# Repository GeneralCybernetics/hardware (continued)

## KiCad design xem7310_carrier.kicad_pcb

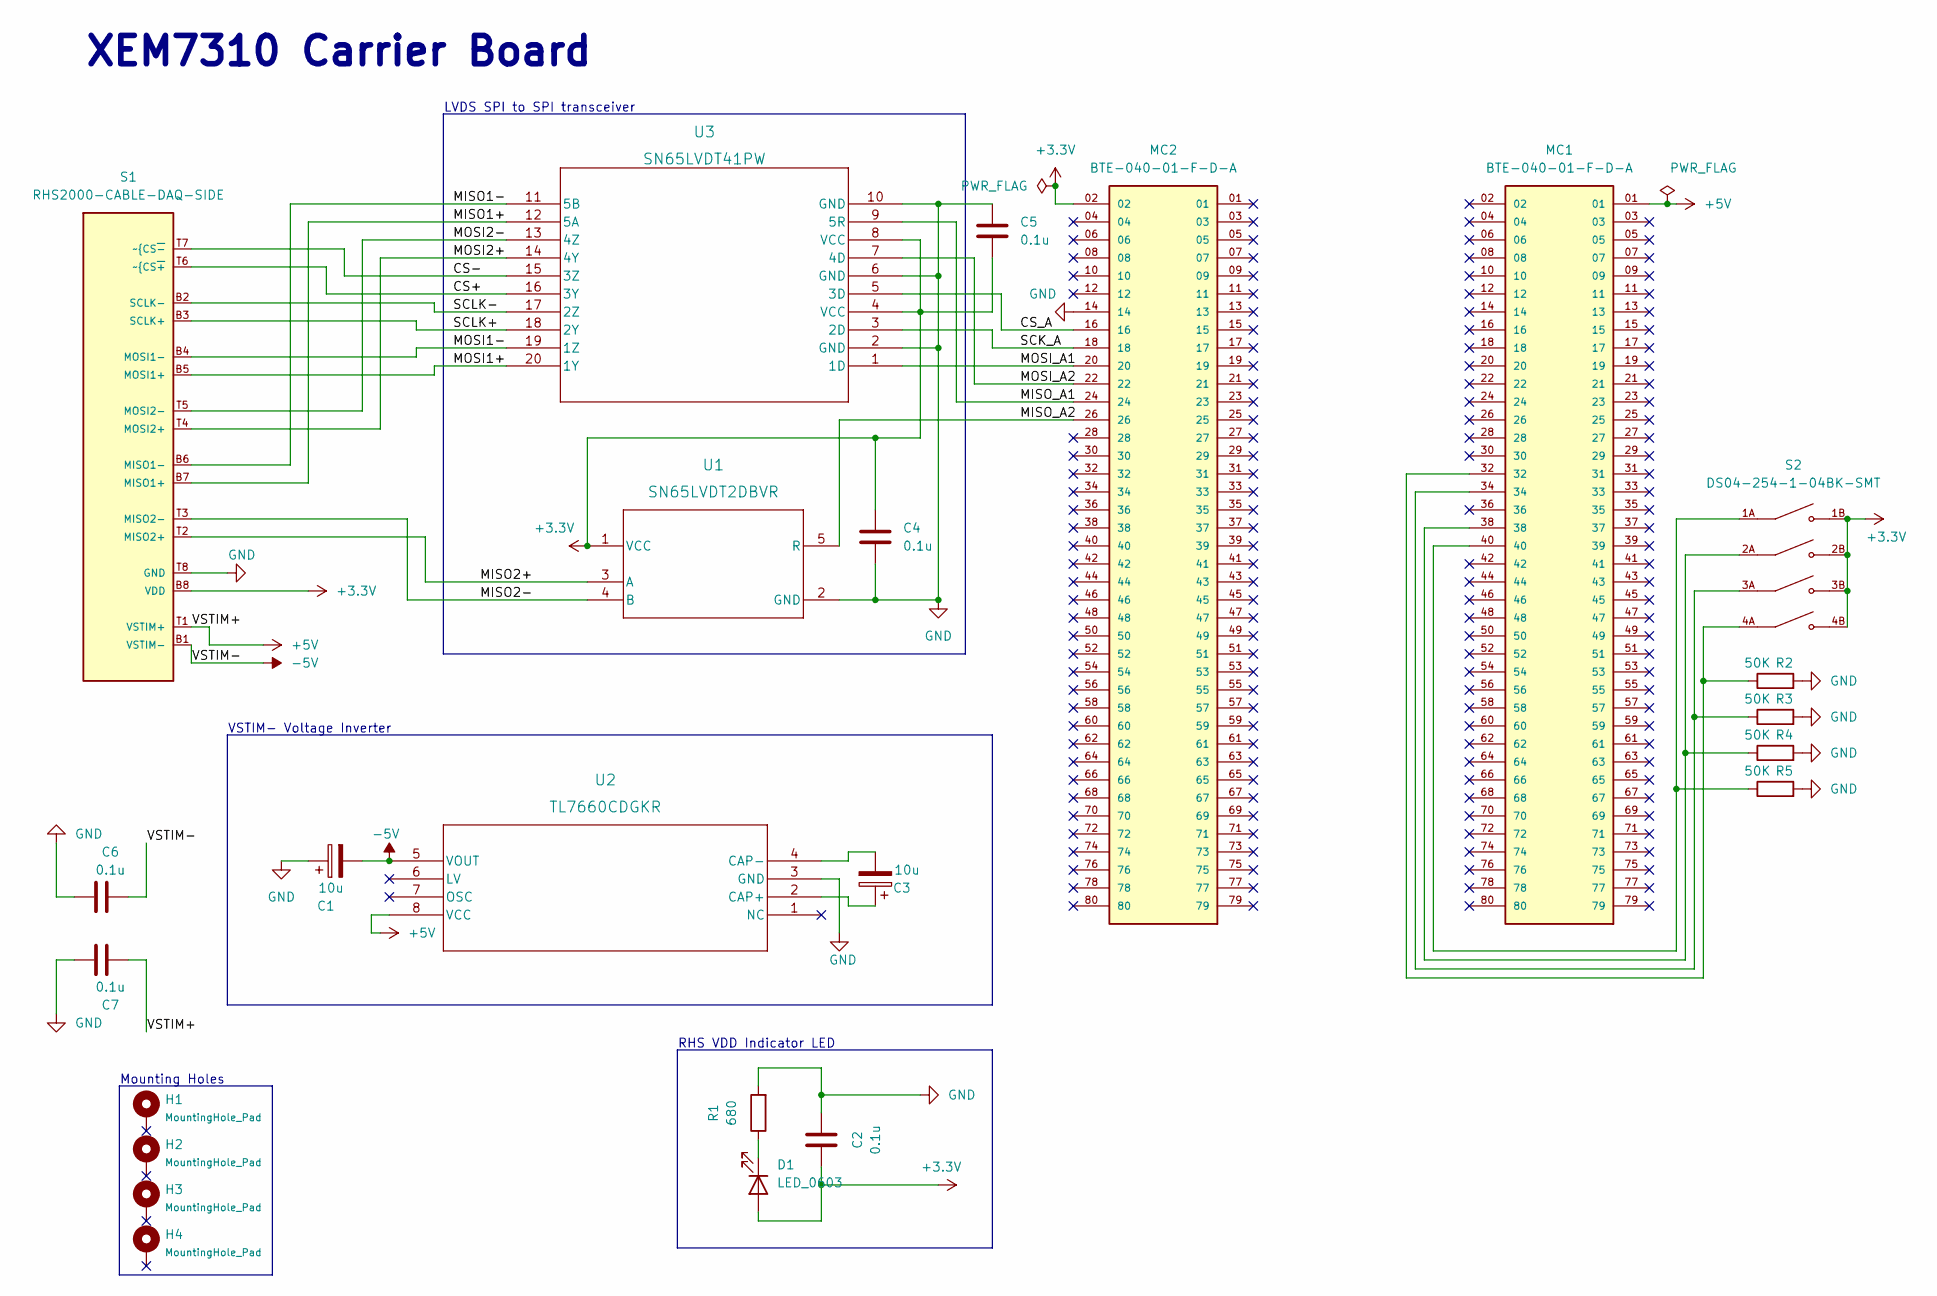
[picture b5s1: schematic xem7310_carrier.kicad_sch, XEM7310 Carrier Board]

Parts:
C1, C3: 10u; CP_Elec_4x5.4
C2, C4, C5, C6, C7: 0.1u; C_0402_1005Metric
D1: LED_0603; LED_0603_1608Metric
H1, H2, H3, H4: MountingHole_Pad; MountingHole_2.7mm_M2.5_DIN965_Pad
MC1, MC2: BTE-040-01-F-D-A; SAMTEC_BTE-040-01-F-D-A; PARTREV R
R1: 680; R_0603_1608Metric
R2, R3, R4, R5: 50K; R_0603_1608Metric
S1: RHS2000-CABLE-DAQ-SIDE
S2: DS04-254-1-04BK-SMT; SW_DS04-254-1-04BK-SMT; PARTREV V0.0
U1: SN65LVDT2DBVR; DBV0005A_N
U2: TL7660CDGKR; DGK8
U3: SN65LVDT41PW; PW20

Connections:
+3.3V: C2.2, C4.1, C5.2, D1.2 (A), MC2.02, S1.B8 (VDD), S2.1B, S2.2B, S2.3B, S2.4B, U1.1 (VCC), U3.4 (VCC), U3.8 (VCC)
+5V: C7.2, MC1.01, S1.T1 (VSTIM+), U2.8 (VCC)
-5V: C1.2, C6.2, S1.B1 (VSTIM-), U2.5 (VOUT)
/CS+: S1.T6 (~CS~{+), U3.16 (3Y)
/CS-: S1.T7 (~CS~{-), U3.15 (3Z)
/CS_A: MC2.16, U3.5 (3D)
/MISO1+: S1.B7 (MISO1+), U3.12 (5A)
/MISO1-: S1.B6 (MISO1-), U3.11 (5B)
/MISO2+: S1.T2 (MISO2+), U1.3 (A)
/MISO2-: S1.T3 (MISO2-), U1.4 (B)
/MISO_A1: MC2.24, U3.9 (5R)
/MISO_A2: MC2.26, U1.5 (R)
/MOSI1+: S1.B5 (MOSI1+), U3.20 (1Y)
/MOSI1-: S1.B4 (MOSI1-), U3.19 (1Z)
/MOSI2+: S1.T4 (MOSI2+), U3.14 (4Y)
/MOSI2-: S1.T5 (MOSI2-), U3.13 (4Z)
/MOSI_A1: MC2.20, U3.1 (1D)
/MOSI_A2: MC2.22, U3.7 (4D)
/SCK_A: MC2.18, U3.3 (2D)
/SCLK+: S1.B3 (SCLK+), U3.18 (2Y)
/SCLK-: S1.B2 (SCLK-), U3.17 (2Z)
GND: C1.1, C2.1, C4.2, C5.1, C6.1, C7.1, MC2.14, R1.2, R2.2, R3.2, R4.2, R5.2, S1.T8 (GND), U1.2 (GND), U2.3 (GND), U3.2 (GND), U3.6 (GND), U3.10 (GND)
unnamed: C3.1, U2.2 (CAP+)
unnamed: C3.2, U2.4 (CAP-)
unnamed: MC1.32, R2.1, S2.4A
unnamed: MC1.34, R3.1, S2.3A
unnamed: MC1.38, R4.1, S2.2A
unnamed: MC1.40, R5.1, S2.1A
unnamed: D1.1 (K), R1.1

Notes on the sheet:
XEM7310 Carrier Board
Mounting Holes
RHS VDD Indicator LED
LVDS SPI to SPI transceiver
VSTIM- Voltage Inverter

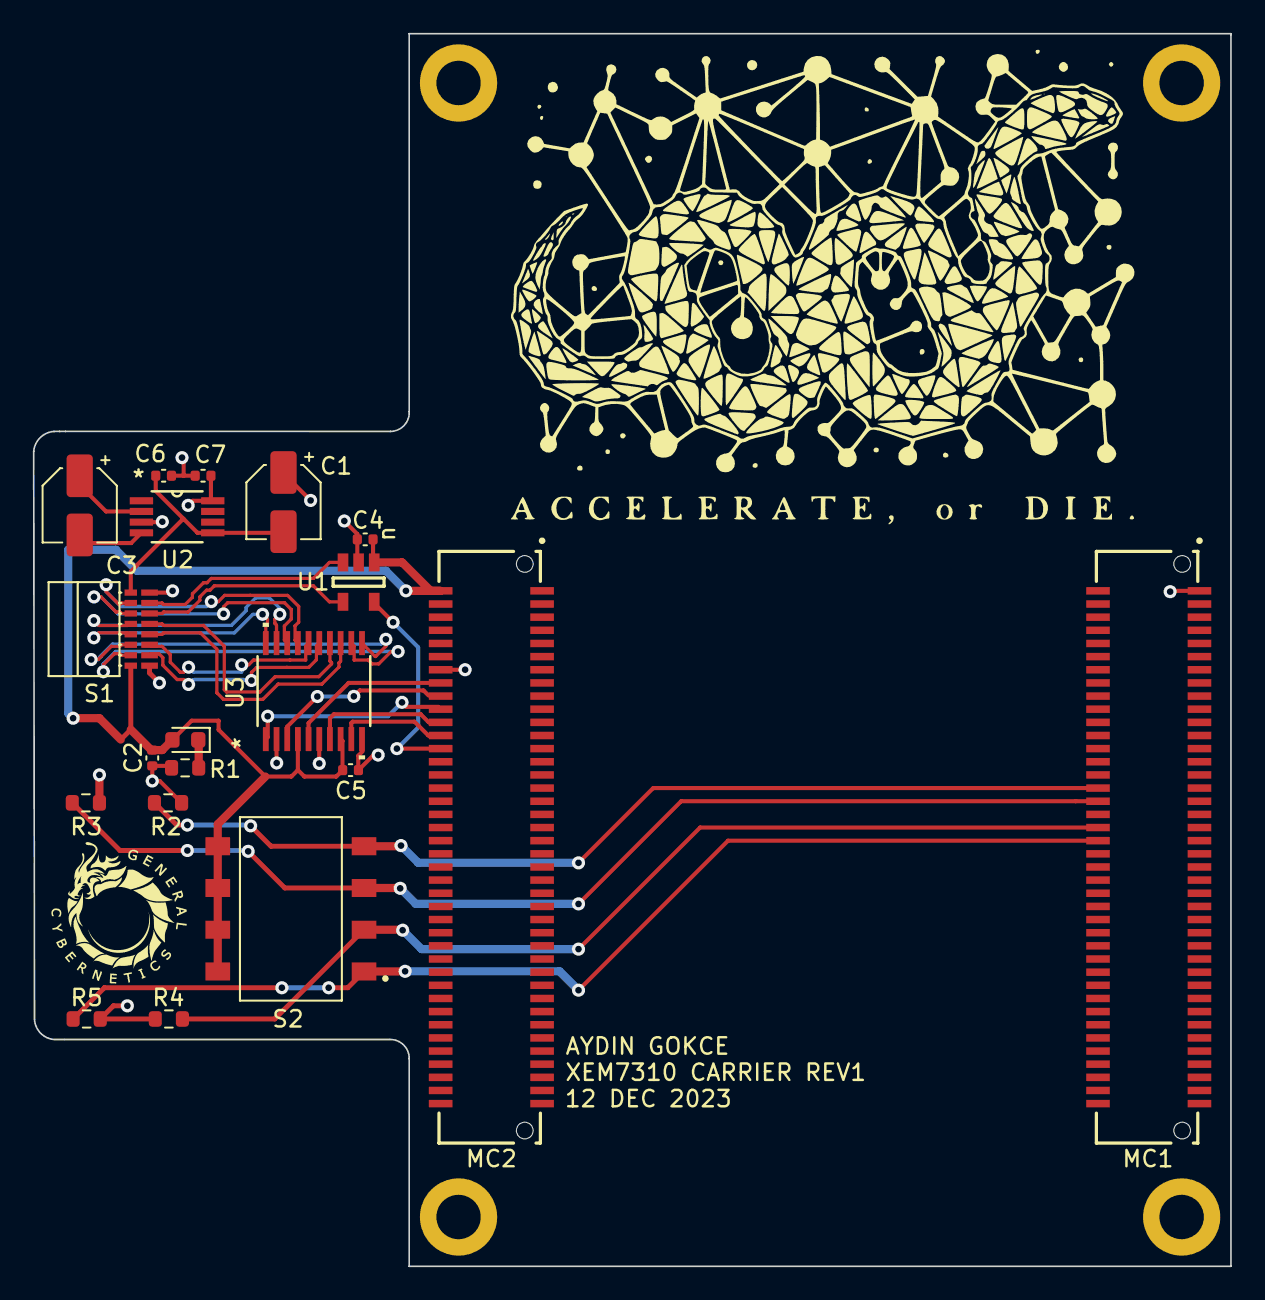
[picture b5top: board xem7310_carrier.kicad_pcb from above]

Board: 4 copper layers, 72.8 x 75.0 mm, 24 parts (0 on the bottom side), 29 nets.

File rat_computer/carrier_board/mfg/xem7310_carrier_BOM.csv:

Comment,Designator,Footprint,"Cost (total, est.)",Notes,Purchase & Datasheet Link
10u,"C1, C3",Capacitor_SMD:CP_Elec_4x5.4,~,Polarized Capacitor,~
0.1u,"C2, C4, C5, C6, C7",Capacitor_SMD:C_0402_1005Metric,~,~,~
LED_0603,D1,LED_SMD:LED_0603_1608Metric,~,Color Green,~
BTE-040-01-F-D-A,"MC1, MC2",BTE-040-01-F-D-A:SAMTEC_BTE-040-01-F-D-A,$17.20,~,https://www.digikey.com/en/products/detail/samtec-inc/BTE-04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
680,R1,Resistor_SMD:R_0603_1608Metric,~,~,~
50K,"R2, R3, R4, R5",Resistor_SMD:R_0603_1608Metric,~,~,~
RHS2000-CABLE-DAQ-SIDE,S1,OMNETICS_PZN-16-AA,$47.48,EXCLUDE FROM ASSEMBLY,~
DS04-254-1-04BK-SMT,S2,DS04-254-1-04BK-SMT:SW_DS04-254-1-04BK-SMT,$0.87,~,https://www.mouser.com/ProductDetail/CUI-Devices/DS04-254-1-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
SN65LVDT2DBVR,U1,FP_LVDT2:DBV0005A_N,$1.85,SOT-23 package,https://www.digikey.com/en/products/detail/texas-instruments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
TL7660CDGKR,U2,TP_TL7660:DGK8,$1.54,8-VSSOP package,https://www.digikey.com/en/products/detail/texas-instruments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
SN65LVDT41PW,U3,FP_LVDT41:PW20,$7.60,20-TSSOP package,https://www.digikey.com/en/products/detail/texas-instruments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

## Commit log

2024-01-04 carrier board
2024-01-17 mea breakout board
2024-01-24 fix: removed soldermask covering pads, lay rows out in the correct square shape
2024-01-26 changed soldermask to black, exported step files
2024-01-26 *actually added step files
2024-01-28 designed carrier board for mp-highdriver
2024-03-14 added keep aliveanator PCB altium project package
2024-08-02 alignment stage done
2024-08-02 completed PT assay led seqs
2024-08-10 EK – microfluidics chip design + documentation
2024-08-10 Changed name of design
2024-08-11 v1.5 updated with full documentation
2024-08-11 Added the md rfc in rfc_md
2024-08-11 removed v1
2024-08-13 refactor: added project-specific subdirectories, added ion concentration biomodulato
2024-08-13 pushing v6
2024-08-13 pushing v7
2024-08-13 refactor: cleanup silkscreen designators
2024-08-13 fix: left-sided highdriver4 pinout (schematic)
2024-08-13 pushing minor v7 changes
2024-08-13 Fix: Switched LED for an 0603 diode
2024-08-16 finished v7 (cleared by DRC)
2024-08-16 V7 fix: Increased area to add mounting holes and pushed receptacles to the edge of board
2024-08-17 Fix: Pulled out the
2024-08-17 Fix: Swapped ground and power planes
2024-08-17 gitignore
2024-08-18 added JLCPCB constraints and gitignore updates
2024-08-18 fix(icbm): update tolerances to comply with new dru
2024-08-18 refactor(icbm): improve capacitor placement
2024-08-18 fix: started adding footprint, symbol and 3dmodel libraries
2024-08-18 Added scripts to improve quality of life when working between remote repo and local KiCAD
2024-08-18 Pushed project_library parser
2024-08-18 Testing add_project_libraries.sh
2024-08-18 Migrated to remote repository use, changing footprints to relative paths
2024-08-18 added co2 sensor 3d model
2024-08-18 pushed all components step files (except 1) for icbm
2024-08-18 fix: moved peltier and co2 solenoid further apart from each other to fit them
2024-08-18 improvements to add_project_libraries.sh
2024-08-18 Finished add_project_libraries script
2024-08-19 fix: Script now asks for input for local file path
2024-08-19 init
2024-08-19 Pushed net changes to v7 ICBM
2024-08-19 testing libraries
2024-08-20 refactor: remove macos malware
2024-08-20 refactor: rearranged everything so it makes sense
2024-08-20 refactor: removed dropped project (for now)
2024-08-20 chore: remove macos malware
2024-08-20 README.md
2024-08-20 feat: automatic project generation
2024-08-20 fix: unfucked footprint and symbol tables
2024-08-22 creating legacy branch before project restructure
2024-08-22 saving before merge
2024-08-22 fix: replaced the USB connector with one in the JLCPCB parts library
2024-08-22 fix: removed macos malware
2024-08-22 feat: delete footprint cache when updating libraries
2024-08-22 fix: Delete .DS_Store
2024-08-22 fix: symlinked common files
2024-08-22 fix: absolute path symlinks -> relative path symlinks
2024-08-22 ci: added anush's components
2024-08-22 fix: refresh libraries script breaking when not in common/kicad
2024-08-24 fix: symbol and footprint libs, and improved routing
2024-08-24 refactor: re-routed icbm
2024-08-24 mfg file for 0.0.8
2024-08-28 fix: move N-channel FETs from high-side to low-side configuration
2024-08-28 fix: ERC errors
2024-08-28 chore: routed MOSFET fixes
2024-08-30 update mfg files
2024-09-01 bioreactor microfluidic chip and keep-aliveinator
2024-09-01 solidworks init
2024-09-01 fix: replace fridge peltier cooler FET with an h-bridge
2024-09-01 chore: specify STEP file
2024-09-01 finished schematic for DC/DC inverter
2024-09-01 updated table with opamp
2024-09-05 designed box & fridge holder
2024-09-05 shrunk lid size, some fixes
2024-09-05 solidworks session wrap-up
2024-09-06 chore: readme update
2024-09-08 ci: main AC/DC schematic done minus incubator peripherals
2024-09-15 fix: added new STM32 with 3 DAC output pins
2024-09-15 ci: added error op amp to ADC
2024-09-15 ci: added to error op amp to ADC
2024-09-16 ci: added DC/DC converters to drop 60V to all required power supplies
2024-09-18 fix: bigger STM32, fix mirrored highdriver pinout
2024-09-18 final manufacturing file
2024-09-30 CI: footprint assignment done
2024-09-30 ci: STM32 layout done and schematic annotated
2024-10-02 ci: layout done
2024-10-07 GND vias added
2024-10-09 fix: new co2 sensor
2024-10-13 ci: adding LTspice files
2024-10-25 fix: replaced op amp with voltage divider for ADC
2024-11-01 layout finalized
2024-11-03 removed trash
2024-11-03 chore: add 96 well plate to common/
2024-11-05 fix: DRV8873 nSLEEP and nFAULT pull-ups
2024-11-05 fix: HSE for USB FS
2024-11-07 feat: oscillator plus mfg files
2024-11-12 finished routing power supplies
2024-11-24 ci: finished routing for signal side
2024-11-26 CI: v1 routing complete
2024-11-27 ci: silkscreen cleaned up
2024-11-29 fix: update DRC constraints and fixed via DRC errors
2024-11-30 fix: cleared all DRC errors
2024-11-30 ci: moved silkscreen items
2024-11-30 fix: updated old footprints
2025-01-01 all drc errors cleared
2025-01-02 fixed some more clearance errors
2025-01-04 BOM in progress
2025-01-08 fixed values for resistive divider of LDOs
2025-01-13 BOM in progress v2
2025-01-13 ci: converting file ./refresh_libraries.sh to Unix format and gitignoring all symlinked tables
2025-01-16 ci: BOM done
2025-01-16 ci: replaced digital pot with one thats available in JLCPCB
2025-01-22 ci: fixed all relevant DRC errors with new components
2025-01-22 ci: manufacturing files generated
2025-01-22 ci: build files for v0.0.2 generated
2025-01-22 cleaning up repo
2025-01-23 ci: v0.0.3 manufacturing files uploaded
2025-01-23 ordered parts
2025-02-13 fix: updated mismatched cap packages
2025-02-14 fix: fixed footprint for problematic mosfet
